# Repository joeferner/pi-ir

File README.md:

Misc
----

1. ```sudo apt-get install avahi-daemon``` (Install mDNS to allow hostname to work).

Change host name
----------------

1. Edit ```/etc/hosts```. Change ```raspberrypi``` to ```basementpi```.
1. Edit ```/etc/hostname```. Change ```raspberrypi``` to ```basementpi```.
1. Run ```sudo /etc/init.d/hostname.sh```

Install LIRC
------------

See http://alexba.in/blog/2013/01/06/setting-up-lirc-on-the-raspberrypi/

1. ```sudo apt-get install lirc```
1. Edit ```/etc/modules```. Add the following:
    
        lirc_dev
        lirc_rpi gpio_in_pin=23 gpio_out_pin=22

1. Edit ```/etc/lirc/hardware.conf```

        # Arguments which will be used when launching lircd
        LIRCD_ARGS=""

        # Don't start lircmd even if there seems to be a good config file
        # START_LIRCMD=false

        # Don't start irexec, even if a good config file seems to exist.
        # START_IREXEC=false

        # Try to load appropriate kernel modules
        LOAD_MODULES=true

        # Run "lircd --driver=help" for a list of supported drivers.
        DRIVER="default"
        # usually /dev/lirc0 is the correct setting for systems using udev
        DEVICE="/dev/lirc0"
        MODULES="lirc_rpi"

        # Default configuration files for your hardware if any
        LIRCD_CONF=""
        LIRCMD_CONF=""

1. Run ```sudo mkdir /etc/lirc/remotes```
1. Copy remote files into ```/etc/lirc/remotes```
1. ```cat``` remote files into ```/etc/lircd.conf```.
1. Run ```sudo /etc/init.d/lirc restart```

Install Node
------------

1. ```wget http://nodejs.org/dist/v0.10.2/node-v0.10.2-linux-arm-pi.tar.gz```
1. ```tar xzf node*```
1. ```sudo mv node* /opt/```
1. ```sudo ln -s /opt/node* /opt/node```
1. ```sudo ln -s /opt/node/bin/node /usr/bin/node```

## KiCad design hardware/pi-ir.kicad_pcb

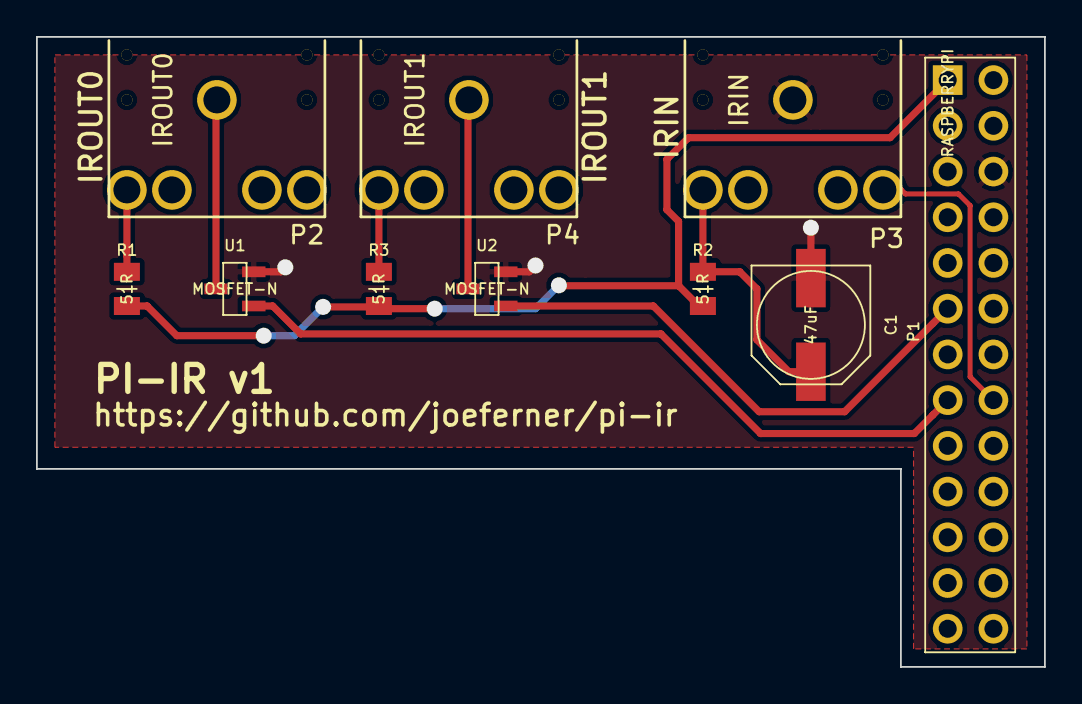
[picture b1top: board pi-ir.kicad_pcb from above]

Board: 2 copper layers, 56.0 x 35.0 mm, 10 parts (0 on the bottom side), 10 nets.

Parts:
C1: 47uF; CAPAE660X790N
P1: RASPBERRYPI; HDRV26W66P254_2X13_3297X503X838P
P2: IROUT0; SJ1-352XNG
P3: IRIN; SJ1-352XNG
P4: IROUT1; SJ1-352XNG
R1, R2, R3: 51R; RESC2012X100N
U1, U2: MOSFET-N; SOT95P237X112_123-3N

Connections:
+3.3V: P1.1, R1.1, R2.1, R3.1
/IRIN: P1.16, P3.3
/IROUT0: P1.15, U1.1
/IROUT1: P1.11, U2.1
GNDPWR: C1.2, P1.6, P3.1, U1.2, U2.2
unnamed: C1.1, P3.2, R2.2
unnamed: P2.1, U1.3
unnamed: P2.2, R1.2
unnamed: P4.1, U2.3
unnamed: P4.2, R3.2

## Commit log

2014-05-29 initial
2014-05-29 simple test driver
2014-05-29 added more commands end events
2014-05-29 better layour
2014-05-30 move kicad library
2014-05-30 schematic done
2014-05-30 added second ir out
2014-05-30 board layout
2014-05-30 add labels
2014-05-31 initial v1 try
2014-05-31 trying to fix README
2014-06-02 remove node code
2014-06-19 add center hole to audio jack and try to fix drill
2014-06-19 update from kicad library
2014-06-19 move push/pull scripts
2017-02-04 update kicad version
